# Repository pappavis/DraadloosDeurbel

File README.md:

# Synopsys
ESP8266 deurbel aan te sluiten op wisselstroom max 20v 1A.

Werk in uitvoering 0.0.1.<br>
<br>

# STATUS:
 - Totally unusable. 
 - Work in progress. 

Deurbel_circuit-20200406-2346.circuitjs simulatie voor <a href="http://lushprojects.com/circuitjs/circuitjs.html">circuitjs</a>

Animatie

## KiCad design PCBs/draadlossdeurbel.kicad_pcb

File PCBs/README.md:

printplaat schema

# Werk in uitvoering!!

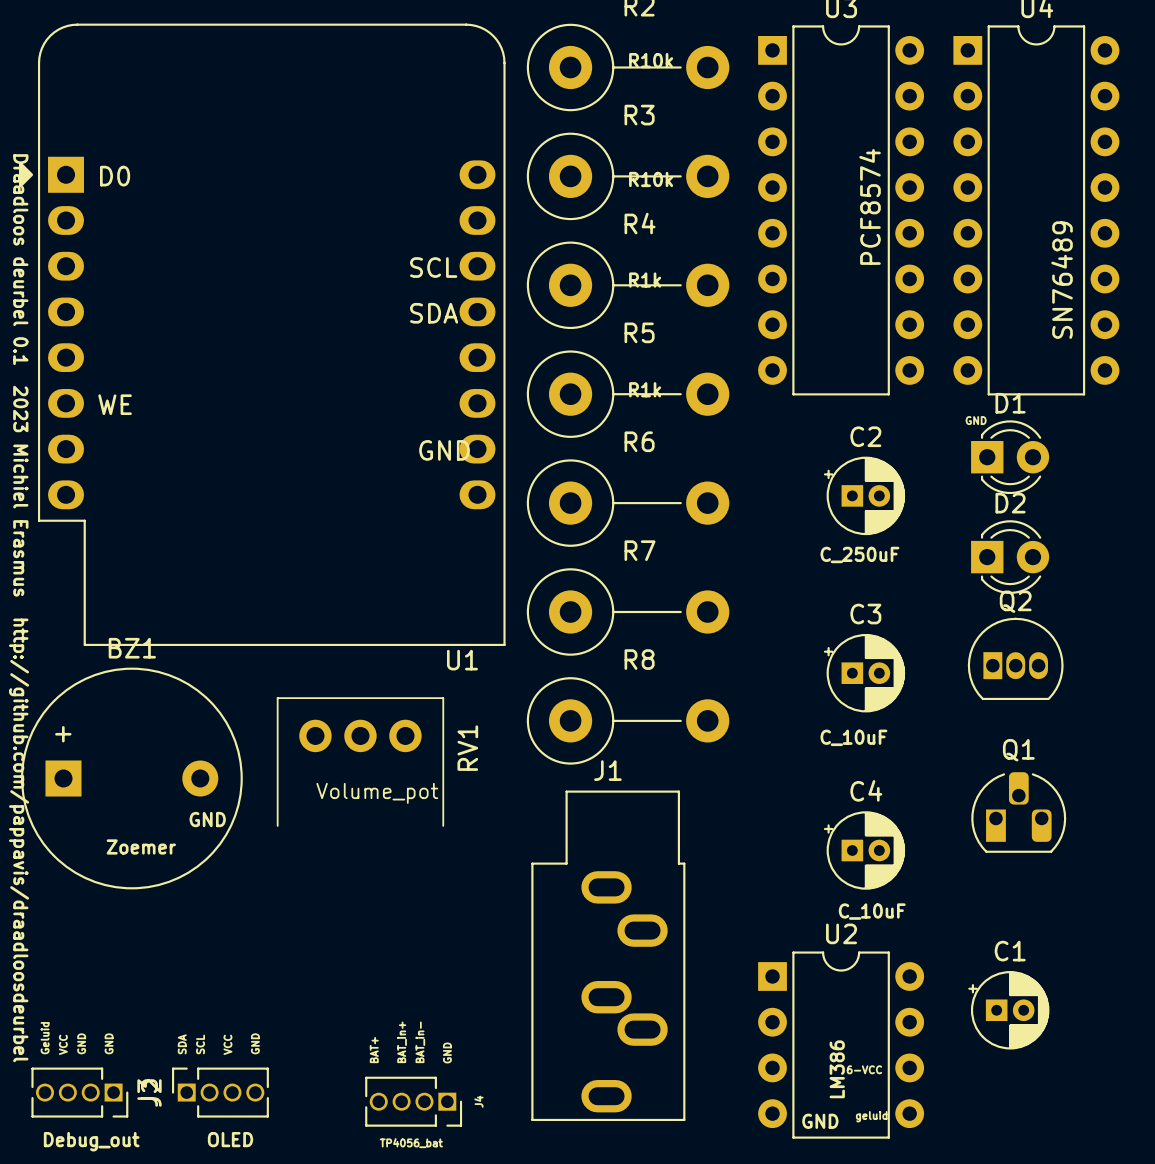
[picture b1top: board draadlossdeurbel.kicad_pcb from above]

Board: 2 copper layers, 25 parts (0 on the bottom side), 32 nets, no tracks yet.

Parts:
BZ1: Zoemer; Buzzer_12x9.5RM7.6
C1, C4: 0.05uF; CP_Radial_D4.0mm_P1.50mm
C2: 250uF; CP_Radial_D4.0mm_P1.50mm
C3: 10uF; CP_Radial_D4.0mm_P1.50mm
D1: LED; LED_D3.0mm
D2: Status_LED; LED_D3.0mm
J1: AudioPlug3; Jack_3.5mm_CUI_SJ1-3535NG_Horizontal
J2: debug_01x04; PinSocket_1x04_P1.27mm_Vertical
J3: I2C_Oled_128X32; PinSocket_1x04_P1.27mm_Vertical
J4: TP4056_bat; PinSocket_1x04_P1.27mm_Vertical
Q1: BC338; TO-92L_HandSolder
Q2: BC338; TO-92_Inline
R2, R4, R5: R10k; R_Axial_DIN0414_L11.9mm_D4.5mm_P7.62mm_Vertical
R3, R8: R1k; R_Axial_DIN0414_L11.9mm_D4.5mm_P7.62mm_Vertical
R6, R7: R100; R_Axial_DIN0414_L11.9mm_D4.5mm_P7.62mm_Vertical
RV1: r_pot_vol; RotaryEncoder_Bourns_Horizontal_PEC09-2xxxF-Nxxxx
U1: WeMos_D1_mini; WEMOS_D1_mini_light
U2: LM386; DIP-8_W7.62mm
U3: PCF8574; DIP-16_W7.62mm
U4: SN76489; DIP-16_W7.62mm

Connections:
/A0: R2.2, U3.1 (A0)
/A1: R4.2, U3.2 (A1)
/AUDIO_UIT: C2.1, C2.2, C4.2, U2.5
AudioPlug3_AanUit: Q2.2 (B), U1.12 (D3)
BAT+: J2.3, J3.3, J4.4, U1.9 (5V), U2.6 (V+), U3.16 (VDD), U4.16 (VCC)
DeepSleep: U1.1 (~RST), U1.3 (D0)
GND: BZ1.2 (+), C3.1, C3.2, C4.1, D2.1 (K), J1.S, J2.1, J2.2, J3.4, J4.1, R2.1, R4.1, R5.1, U1.10 (GND), U2.2 (-), U2.4 (GND), U2.7 (BYPASS), U3.8 (VSS), U4.6 (~OE), U4.8 (GND)
GeluidAanUit: Q1.2 (B), U1.11 (D4)
unnamed: C1.1, U2.8 (GAIN)
unnamed: C1.2, R3.2
unnamed: D1.2 (A), R7.1
unnamed: D1.1 (K), Q2.1 (C)
unnamed: D2.2 (A), R8.2
unnamed: J1.T, R6.2
unnamed: Q2.3 (E), R6.1
unnamed: R3.1, U2.1 (GAIN)
unnamed: R8.1, U1.4 (SCK/D5)
unnamed: R5.2, U3.3 (A2)
PWM_CLK: U1.2 (A0), U4.14 (CLOCK)
Qa: U3.4 (P0), U4.3 (D0)
Qb: U3.5 (P1), U4.2 (D1)
Qc: U3.6 (P2), U4.1 (D2)
Qd: U3.7 (P3), U4.15 (D3)
Qe: U3.9 (P4), U4.13 (D4)
Qf: U3.10 (P5), U4.12 (D5)
Qg: U3.11 (P6), U4.11 (D6)
Qh: U3.12 (P7), U4.10 (D7)
SCL: J3.2, U1.14 (SCL/D1), U3.14 (SCL)
SDA: J3.1, U1.13 (SDA/D2), U3.15 (SDA)
WE: U1.6 (MOSI/D7), U4.5 (~WE)
Zoemer: BZ1.1 (-), Q1.3 (C), R7.2
geluid: J1.R, J2.4, U2.3 (+), U4.7 (AUDIO_OUT)

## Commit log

2020-01-23 eerste commit
2020-02-25 LM358 opamp toevoeging werk-in-uitvoering
2020-04-07 basislogic schema met circuitjs
2020-04-11 LTspice model
2022-12-14 setup
2022-12-14 bijgewerkt
2023-03-27 6581 SID biliotheek toegevoegd
2023-03-28 Wireless Doorbell 0.0.2
2023-03-28 KiCAD weergave
